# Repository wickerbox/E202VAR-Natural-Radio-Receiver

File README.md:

## Introduction

This project is based on the Explorer E202, with permission. 

Renato Romero put plans online for a Very Low Frequency (VLF) receiver capable between "a few Hz to beyond 10 kHz [which] makes it suitable to to receive radio signals of natural origin; signals not generated by human activity but by physical phenomena such as lightning and solar storms. Received signals are heard directly in your headset. The receiver amplifies the electric component of an electromagnetic signal."

His plans are <a href="http://www.vlf.it/romero2/explorer-e202.html">described on the vlf.it website</a>. The Explorer E202 is no longer available for sale.

He gave me permission to work from his schematic to design a new layout and make my own units. I am releasing all of my documents and process under the CERN Open Hardware License v1.2.

This is the original E202 full-size schematic.

\pagebreak

## Assembled v1.1 Receiver with Case

A fully assembled v1.1 in a box looked like this:

\pagebreak

## Assembled v1.4 Receiver Board

The final board for v1.4, which is the release version, looks like this: 

\pagebreak

## Cost

Total cost of parts is about $25 if you order minimums. It's about $100 if you go to the next price break for most at qty=10, which is what I did since I'm prototyping, and what I recommend if you want to build two or more units. 

OSH Park: $35.35 for a set of three bare boards [<a href="https://oshpark.com/shared_projects/NvQSoarW">Shared Project #NvQSoarW</a>]

Digikey cart: $24.40 for parts for one board [<a href="http://www.digikey.com/short/32fqdm">Shared Cart #32fqdm</a>]

<!--- bom start --->
## Bill of Materials

|Ref|Qty|Description|Digikey PN|
|---|---|-----------|------|
|BNC1 BNC2 BNC3|3|CONN BNC JACK R/A 50 OHM PCB|A97555-ND|
|C1|1|CAP CER 0.033UF 50V C0G RADIAL|445-8490-ND|
|C10|1|CAP CER 10000PF 50V C0G RADIAL|445-8384-ND|
|C15 C14|2|CAP CER 0.022UF 50V X7R RADIAL|399-14089-1-ND|
|C16 C7|2|CAP CER 4700PF 50V C0G RADIAL|445-8585-ND|
|C2 C11|2|CAP CER 0.1UF 50V C0G RADIAL|445-8532-ND|
|C3|1|CAP CER 8.2PF 50V NP0 RADIAL|399-8923-ND|
|C5|1|CAP CER 150PF 50V NP0 RADIAL|BC1015CT-ND|
|C6 C12 C4|3|CAP CER 10UF 16V X5R RADIAL|445-8290-ND|
|C9 C13|2|CAP CER 100UF 6.3V X5R RADIAL|445-8441-ND|
|D1 D2|2|DIODE GEN PURP 50V 1A DO41|1N4001-TPMSCT-ND|
|D3|1|LED BLUE CLEAR 5MM ROUND T/H|C503B-BCS-CV0Z0461-ND|
|J1 J4|2|CONN PWR JACK 2.5X5.5MM HIGH CUR|PJ-202BH|
|J2 J5|2|CONN TERM SCREW GREEN 2.54MM 2POS TH|ED10561-ND|
|J3|1|CONN JACK STEREO R/A 3PIN 3.5MM|CP1-3523N-ND|
|L1|1|FIXED IND 3.3UH 575MA 300 MOHM|78F3R3J-RC-ND|
|LAMP1|1|LAMP NEON 6.2MM WIRE TERMINAL|A9A-ND|
|Q1 Q2|2|TRANS NPN 45V 0.1A TO-92|BC547BTACT-ND|
|R10|1|POT 10K OHM 1/5W PLASTIC LINEAR|987-1301-ND|
|R11|1|RES 4.7K OHM 1/4W 5% CF MINI|S4.7KQCT-ND|
|R12|1|RES 2.2K OHM 1/4W 5% CARBON FILM|CF14JT2K20CT-ND|
|R13|1|RES 1K OHM 1/4W 5% CF MINI|S1KQCT-ND|
|R4|1|RES 3.3K OHM 1/4W 5% CARBON FILM|CF14JT3K30CT-ND|
|R5 R1|2|RES 10M OHM 1/4W 5% CARBON FILM|CF14JT10M0CT-ND|
|R6 R2 R3|3|RES 100K OHM 1/4W 5% CARBON FILM|CF14JT100KCT-ND|
|R7|1|RES 10 OHM 1/4W 5% CARBON FILM|CF14JT10R0CT-ND|
|R8|1|RES 10K OHM 1/4W 5% CF MINI|S10KQCT-ND|
|R9 R17|2|RES 33 OHM 1/4W 5% CARBON FILM|CF14JT33R0CT-ND|
|U1|1|IC REG LDO 9V 1A MC7809 TO220AB|MC7809CTGOS-ND|
|U2|1|IC VREF GND REF ADJ TO92|296-6549-5-ND|
|U3|1|IC AUDIO PWR AMP LOW VOLT 8-DIP|NJM386D-ND|
|U4|1|IC OPAMP JFET 3MHZ DIP8|296-7203-5-ND|

<!--- bom end --->

\pagebreak

## Gerber Preview

\pagebreak

## Assembly Diagram

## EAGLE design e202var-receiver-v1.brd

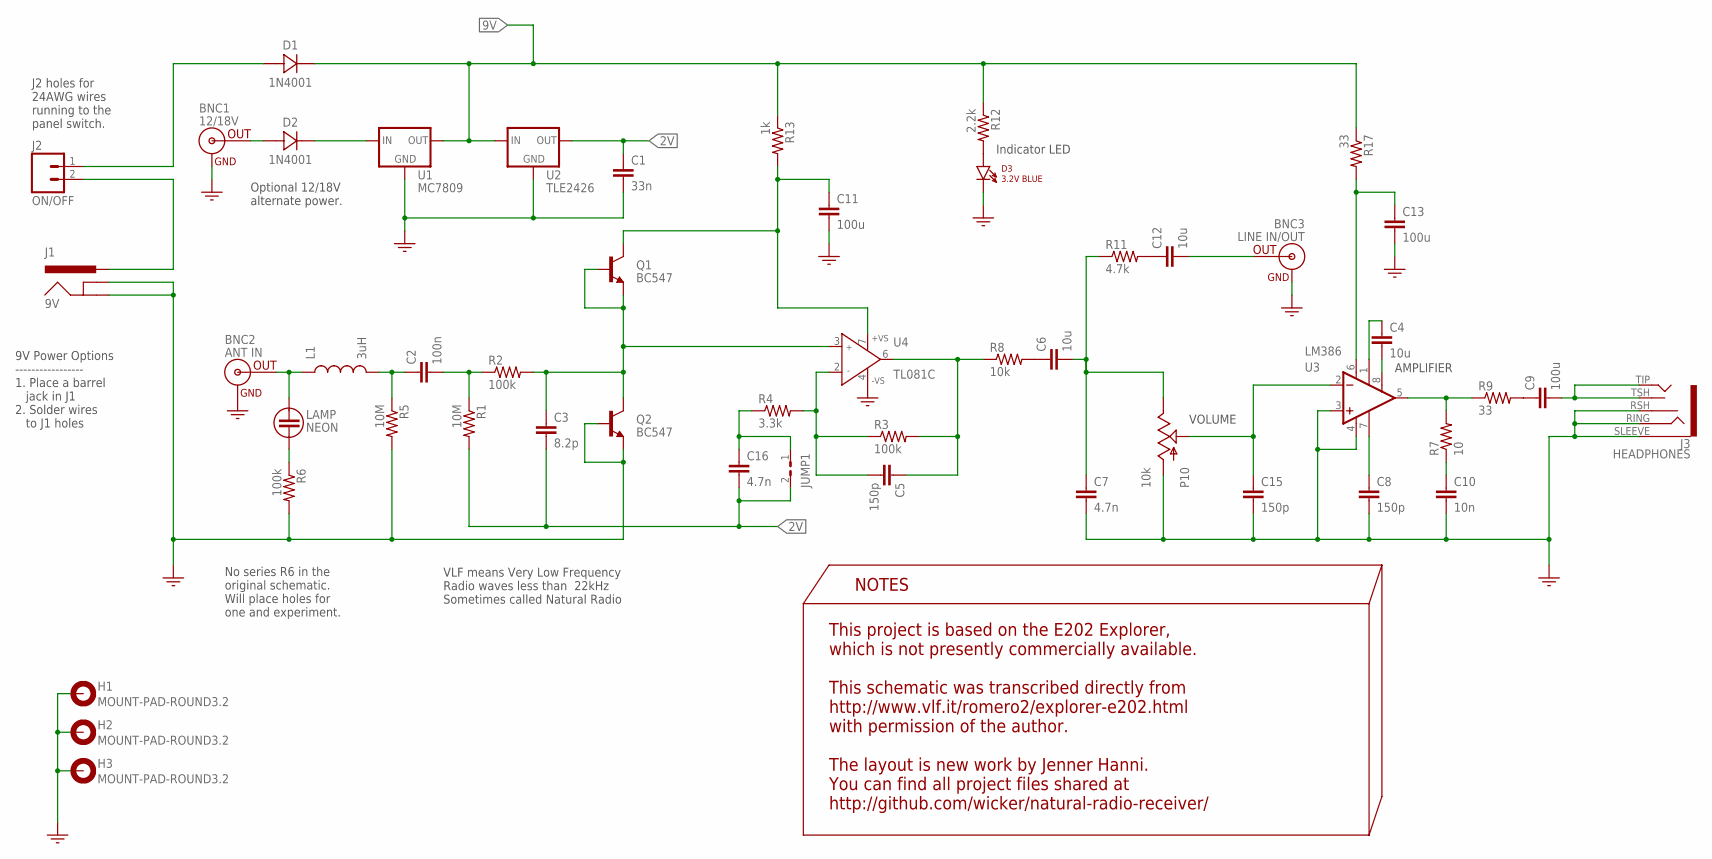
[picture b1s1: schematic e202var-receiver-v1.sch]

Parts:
BNC1: 12/18V; BNC-MOLEX-SD-73100
BNC2: ANT IN; BNC-MOLEX-SD-73100
BNC3: LINE IN/OUT; BNC-MOLEX-SD-73100
C1: 33n; CAP-RADIAL-5MM-NONPOL
C2: 100n; CAP-RADIAL-5MM-NONPOL
C3: 8.2p; CAP-RADIAL-5MM-NONPOL
C4, C6, C12: 10u; CAP-RADIAL-2.5MM-NONPOL
C5, C8, C15: 150p; CAP-RADIAL-2.5MM-NONPOL
C7, C16: 4.7n; CAP-RADIAL-5MM-NONPOL
C9, C11, C13: 100u; CAP-RADIAL-5MM-NONPOL
C10: 10n; CAP-RADIAL-2.5MM-NONPOL
D1, D2: 1N4001; DIODE-DO41
D3: 3.2V BLUE; LED-2PIN-0.1IN
H1, H2, H3: MOUNT-PAD-ROUND3.2; 3,2-PAD
J1: 9V; JACK-POWER
J2: ON/OFF; CONN-2PIN-0.1IN
J3: HEADPHONES; JACK-AUDIO-5PIN
JUMP1: HPF; CONN-2PIN-0.1IN
L1: 3uH; RES-CF14-TH
LAMP: NEON; LAMP-2PIN-0.1IN
P10: 10k; POT-3PIN-LINEAR
Q1, Q2: BC547; TO-92-AMMO
R1, R5: 10M; RES-CF14-TH
R2, R3, R6: 100k; RES-CF14-TH
R4: 3.3k; RES-CF14-TH
R7: 10; RES-CF14-TH
R8: 10k; RES-CF14-TH
R9, R17: 33; RES-CF14-TH
R11: 4.7k; RES-CF14-TH
R12: 2.2k; RES-CF14-TH
R13: 1k; RES-CF14-TH
U1: MC7809; TO-220
U2: TLE2426; DIP-08
U3: LM386; DIP-08
U4: TL081C; DIP-08

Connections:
2V: C1.1, C3.2, C16.2, JUMP1.2, R1.P$2 (2), U2.1 (OUT)
9V: D1.C (CATHODE), R12.P$1 (1), R13.P$1 (1), R17.P$1 (1), U1.OUT, U2.3 (IN)
9V1: J1.PWR, J2.2
9V2: D1.A (ANODE), J2.1
GND: BNC1.GND, BNC1.GND1 (GND), BNC2.GND, BNC2.GND1 (GND), BNC3.GND, BNC3.GND1 (GND), C1.2, C7.2, C8.2, C10.2, C11.2, C13.2, C15.2, D3.C (CATHODE), H1.B3,2, H2.B3,2, H3.B3,2, J1.GND, J1.GNDBREAK, J3.RING, J3.RSH, J3.SLEEVE, P10.1 (A), Q2.2 (B), Q2.3 (E), R5.P$2 (2), R6.P$2 (2), U1.GND, U2.2 (GND), U3.3 (+IN), U3.4 (V-), U4.4 (-VS)
unnamed: C11.1, Q1.1 (C), R13.P$2 (2), U4.7 (+VS)
unnamed: BNC2.SIGNAL (OUT), L1.P$1 (1), LAMP.A (1)
unnamed: C5.2, R3.P$1 (1), R4.P$2 (2), U4.2 (IN-)
unnamed: C2.1, L1.P$2 (2), R5.P$1 (1)
unnamed: C2.2, R1.P$1 (1), R2.P$1 (1)
unnamed: C16.1, JUMP1.1, R4.P$1 (1)
unnamed: C6.1, R8.P$2 (2)
unnamed: C5.1, R3.P$2 (2), R8.P$1 (1), U4.6 (OUT)
unnamed: C6.2, C7.1, P10.3 (E), R11.P$1 (1)
unnamed: C12.1, R11.P$2 (2)
unnamed: C4.1, U3.1 (GAIN)
unnamed: BNC3.SIGNAL (OUT), C12.2
unnamed: C4.2, U3.8 (GAIN)
unnamed: C13.1, R17.P$2 (2), U3.6 (V+)
unnamed: C8.1, U3.7 (BP)
unnamed: C15.1, P10.2 (S), U3.2 (-IN)
unnamed: D3.A (ANODE), R12.P$2 (2)
unnamed: R7.P$2 (2), R9.P$1 (1), U3.5 (OUT)
unnamed: C9.1, R9.P$2 (2)
unnamed: C9.2, J3.TIP, J3.TSH
unnamed: C10.1, R7.P$1 (1)
unnamed: LAMP.C (2), R6.P$1 (1)
Q1OUT: C3.1, Q1.2 (B), Q1.3 (E), Q2.1 (C), R2.P$2 (2), U4.3 (IN+)
VIN: BNC1.SIGNAL (OUT), D2.A (ANODE)
VIN2: D2.C (CATHODE), U1.IN

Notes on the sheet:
This project is based on the E202 Explorer, which is not presently commercially available. This schematic was transcribed directly from http://www.vlf.it/romero2/explorer-e202.html with permission of the author. The layout is new work by Jenner Hanni. You can find all project files shared at http:/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
NOTES
VOLUME
9V Power Options ----------------- 1. Place a barrel jack in J1 2. Solder wires to J1 holes
J2 holes for 24AWG wires running to the panel switch.
Optional 12/18V alternate power.
No series R6 in the original schematic. Will place holes for one and experiment.
Indicator LED
VLF means Very Low Frequency Radio waves less than 22kHz Sometimes called Natural Radio
AMPLIFIER

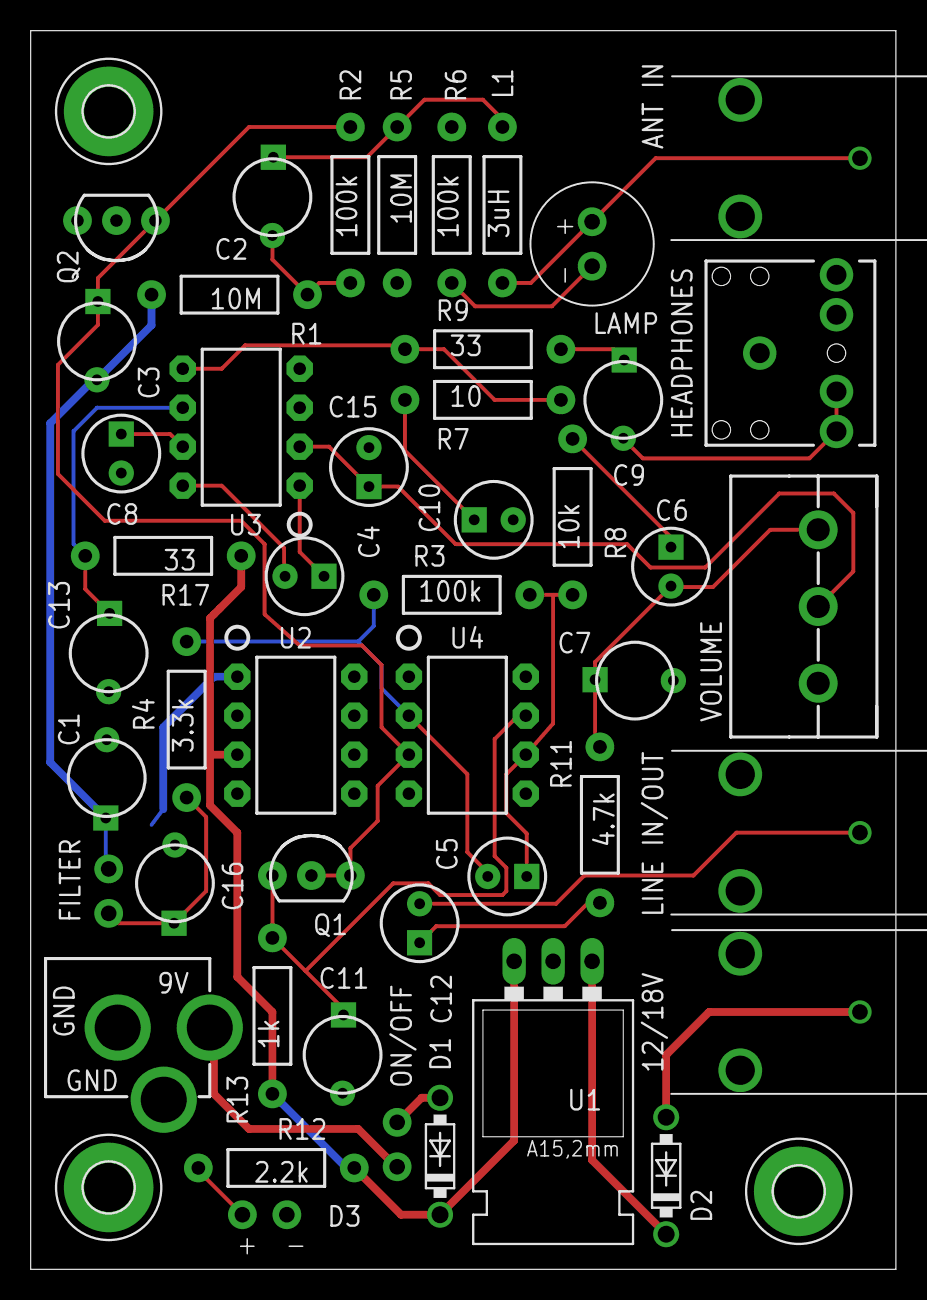
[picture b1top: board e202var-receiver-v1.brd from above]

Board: 2 copper layers, 56.4 x 80.7 mm, 50 parts (0 on the bottom side), 30 nets.

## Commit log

2015-10-16 Added license.
2015-10-16 Added BOM.
2015-10-20 Added notes, clarified BOM a little.
2015-10-20 Finished first pass of schematic. Ready for review.
2015-10-24 Changed name. Cleaned up schematic. Added notes and exported BOM. Need to compare.
2015-10-24 Updated README.
2015-10-24 Added image to readme.
2015-10-24 Checking spaces in BOM.
2015-10-24 Finished capacitors and diodes.
2015-10-24 Tweaks!
2015-10-24 Added resistors.
2015-10-24 Parts selected! BOM created! (For now...)
2015-10-24 Cleaned up the notes. Final. Ready to merge.
2015-10-25 Changed R7 so all resistors are from same family.
2015-10-25 Changed R7, checked off verified BOM todo item.
2015-10-25 Changed LAMP(A) to a 4mm neon indicator. Added cost.
2015-10-25 Adding spot for R6 for testing. Possible DNP.
2015-10-25 Changed OP1 refdes to U4
2015-10-25 Added datasheets for most of the parts.
2015-10-25 Added e202var library and clean schematic.
2015-10-25 Made sure README and BOM.md agree on final BOM.
2015-10-25 Fixing the broken markdown table.
2015-10-25 Updated schematic PNG image from schematic.
2015-10-25 Added frame. Regenerated image.
2015-10-25 Placed components. Board size probably 2.22x3.18 inches. 5.25 for three at OSH Park.
2015-10-25 Finished layout.
2015-10-25 Added schematic, layout, and OSH Park preview images.
2015-10-25 Added CAM, DRU, clean BOM, library, and final of everything. Now we wait for Oct 30th.
2015-12-19 Version 1.1 draft, awaiting last round of testing.
2015-12-19 Getting the repo set up for v1.1
2015-12-19 Finished a sentence, added images.
2016-12-06 Created Kicad schematic for v1.1.
2016-12-09 Rough part placement. Created README. Images made by gerbv are off-center.
2016-12-10 Added parts. Ready for layout.
2016-12-10 Ported the board to KiCad.
2016-12-10 Release v1.2
2016-12-10 Clarified sections in README.
2016-12-10 Argh. typo.
2016-12-10 Cleanup
2016-12-26 v1.3 fixes in place. Saving before running script.
2016-12-26 Moved folders around.
2016-12-26 Playing with kingfisher.
2016-12-27 v1.3 release.
2016-12-27 Fix v1.3 PDF. Order boards.
2016-12-27 Added OSH Park link.
2017-02-23 Fixed several schematic issues.
2017-02-23 v1.4 because of silly schematic mistakes.
2017-02-24 Added three mounting holes to v1.4. Release.
2017-03-14 Release v1.4. Verified build. Project complete.
2017-03-15 Added v1.4 assembled image.

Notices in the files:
parts and their libraries:
max-viz: IN THIS DRAWING UNDER THE TERMS OF THE
CERN OPEN HARDWARE LICENSE 1.2.
